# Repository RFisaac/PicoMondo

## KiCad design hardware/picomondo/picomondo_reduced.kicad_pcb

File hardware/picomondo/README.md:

# PicoMondo working project

Open `picomondo_reduced.kicad_pro` in KiCad 10.

This is the live design: v1 as ordered, plus changes made since. Anything here may be half-finished. To build or debug the boards that were actually made, use `../archive/v1-as-ordered/` instead.

## Changes since the v1 order

- **PSRAM (in progress, paused):** U16 APS6404L-3SQR (SOIC-8) and C71 100 nF added on the MCU sheet (2026-11-03) as an optional second QSPI memory. The schematic symbol is a W25Q128JVS borrowed for its pinout. It is placed on the board but not finished or checked.

## Sheets

| Sheet | Contents |
|---|---|
| `mcu_core` | RP2350B, VREG, crystal, flash, PSRAM, BOOTSEL/RESET, SWD |
| `barrel_input` | Barrel jack, PTC fuse, TVS, LM74502 reverse/overvoltage cut-off |
| `power_5v` | LMR33630B buck and the USB/barrel diode OR |
| `power_3v3` | AP2112K-3.3 LDO |
| `usb_c` | USB-C receptacle, CC resistors, ESD |
| `switched_output` | High-side P-FET output, INA226 monitor, fuse, flyback |
| `edgelock` | EdgeLock connectors, header holes, 100 Ω series resistors |
| `io_indicators` | Per-GPIO indicator LED ring |
| `neopixel` | NeoPixel buffer and connector, Qwiic |
| `board_support` | microSD, status/user/power LEDs, I2C pull-ups, test points |

## Libraries

- `lib/picomondo.pretty`: custom footprints (EdgeLock with 1.0 mm notches, header-hole and heavy-hole variants, RP2350 QFN-80 with thermal vias, polarity-marked VREG inductor, small-pad 0402).
- `lib/lcsc/`: parts converted from LCSC/EasyEDA with `easyeda2kicad`, with 3D models.
- `lib/MCU_RaspberryPi_RP2350.kicad_sym`: Raspberry Pi's RP2350 symbol.
- `JLCImport.*`: the JST-XH NeoPixel connector. One 3D model (`XY-SM04B-SRSS-TB.wrl`, the Qwiic connector) points at a global `${KICAD10_3RD_PARTY}` library and only shows if you have it installed.

## Fabrication

JLCPCB output is made with the Fabrication Toolkit plugin (settings in `fabrication-toolkit-options.json`). Generated `production/`, `jlcpcb/` and `bom/` folders are git-ignored here; the files that were actually ordered are in `../archive/v1-as-ordered/jlc_order_files/`.

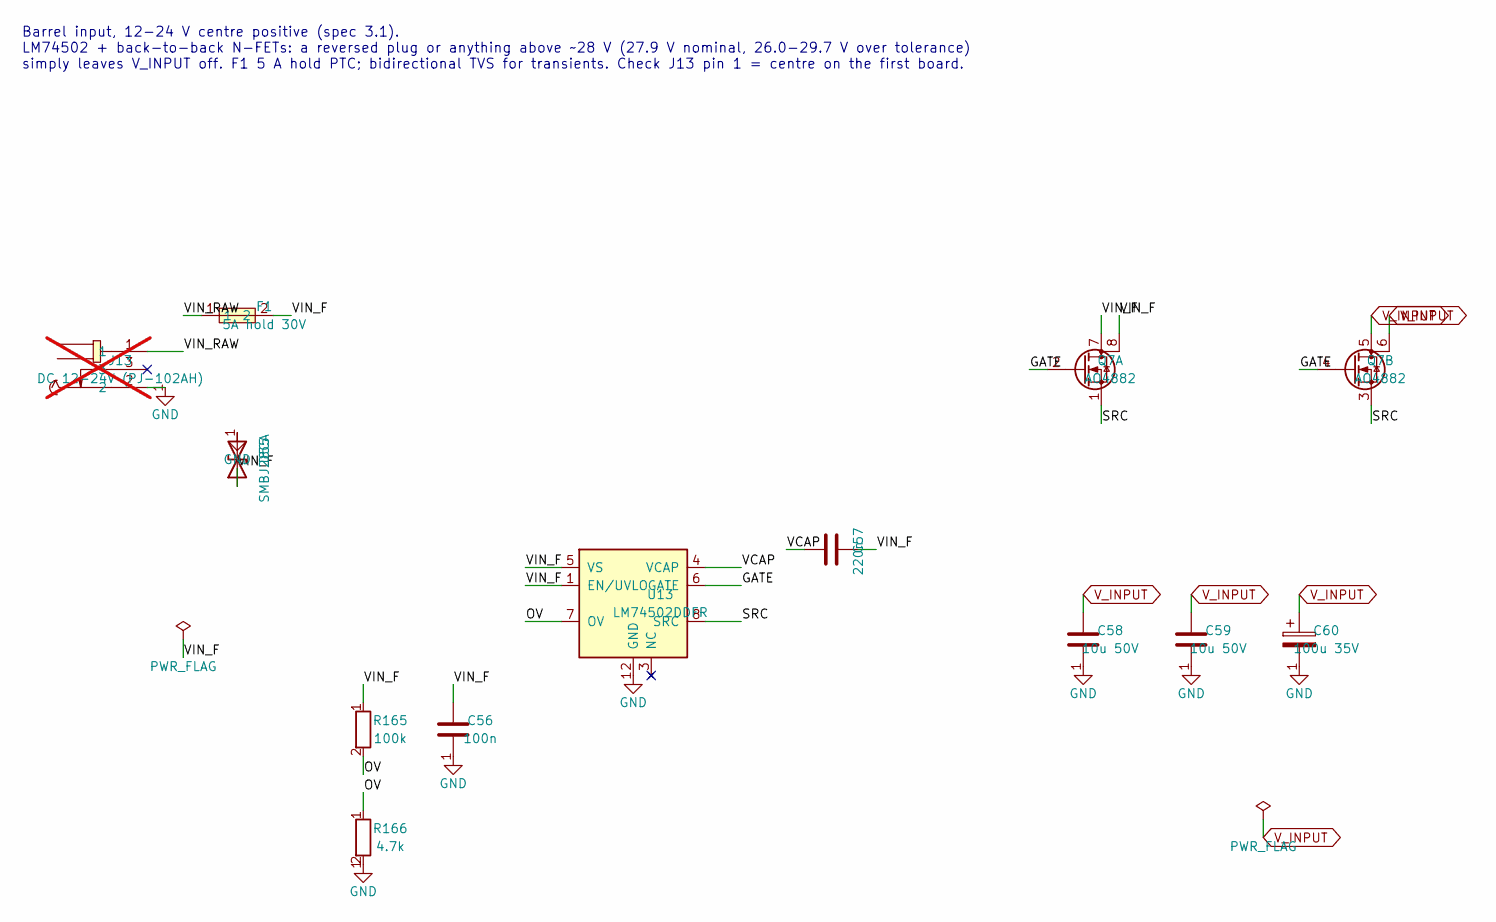
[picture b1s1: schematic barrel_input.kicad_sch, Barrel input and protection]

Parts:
C56: 100n; C_0402_1005Metric; MPN CL05B104KB54PNC; LCSC C307331
C57: 220n; C_0402_1005Metric; MPN C1005X7R1E224K050BB
C58, C59: 10u 50V; C_1206_3216Metric; MPN CL31A106KBHNNNE; LCSC C13585
C60: 100u 35V; CP_Elec_6.3x7.7; MPN VT1V101MCRE77; LCSC C294520
D55: SMBJ28CA; D_SMB; MPN SMBJ28CA; LCSC C8836
F1: 5A hold 30V; F2920; MPN 2920L500/30GR; LCSC C19078763
J13: DC 12-24V (PJ-102AH); DC-IN-TH_PJ-102AH; MPN PJ-102AH; LCSC C3096093; not fitted
Q7: AO4882; SOIC-8_3.9x4.9mm_P1.27mm; MPN AO4882; LCSC C477943
R165: 100k; R_0402_1005Metric; MPN 0402WGF1003TCE; LCSC C25741
R166: 4.7k; R_0402_1005Metric; MPN 0402WGF4701TCE; LCSC C25900
U13: LM74502DDFR; SOT-23-8; MPN LM74502DDFR; LCSC C3236215

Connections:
/Barrel input/GATE: Q7.2 (G), Q7.4 (G), U13.6 (GATE)
/Barrel input/OV: R165.2, R166.1, U13.7 (OV)
/Barrel input/SRC: Q7.1 (S), Q7.3 (S), U13.8 (SRC)
/Barrel input/VCAP: C57.1, U13.4 (VCAP)
/Barrel input/VIN_F: C56.1, C57.2, D55.1 (A1), F1.2, Q7.7 (D), Q7.8 (D), R165.1, U13.1 (EN/UVLO), U13.5 (VS)
/Barrel input/VIN_RAW: F1.1, J13.1
GND: C56.2, C58.2, C59.2, C60.2, D55.2 (A2), J13.2, R166.2, U13.2 (GND); also elsewhere on the board
V_INPUT: C58.1, C59.1, C60.1, Q7.5 (D), Q7.6 (D); also elsewhere on the board

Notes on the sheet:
Barrel input, 12-24 V centre positive (spec 3.1). LM74502 + back-to-back N-FETs: a reversed plug or anything above ~28 V (27.9 V nominal, 26.0-29.7 V over tolerance) simply leaves V_INPUT off. F1 5 A hold PTC; bidirectional TVS for transients. Check J13 pin 1 = centre on the first board.

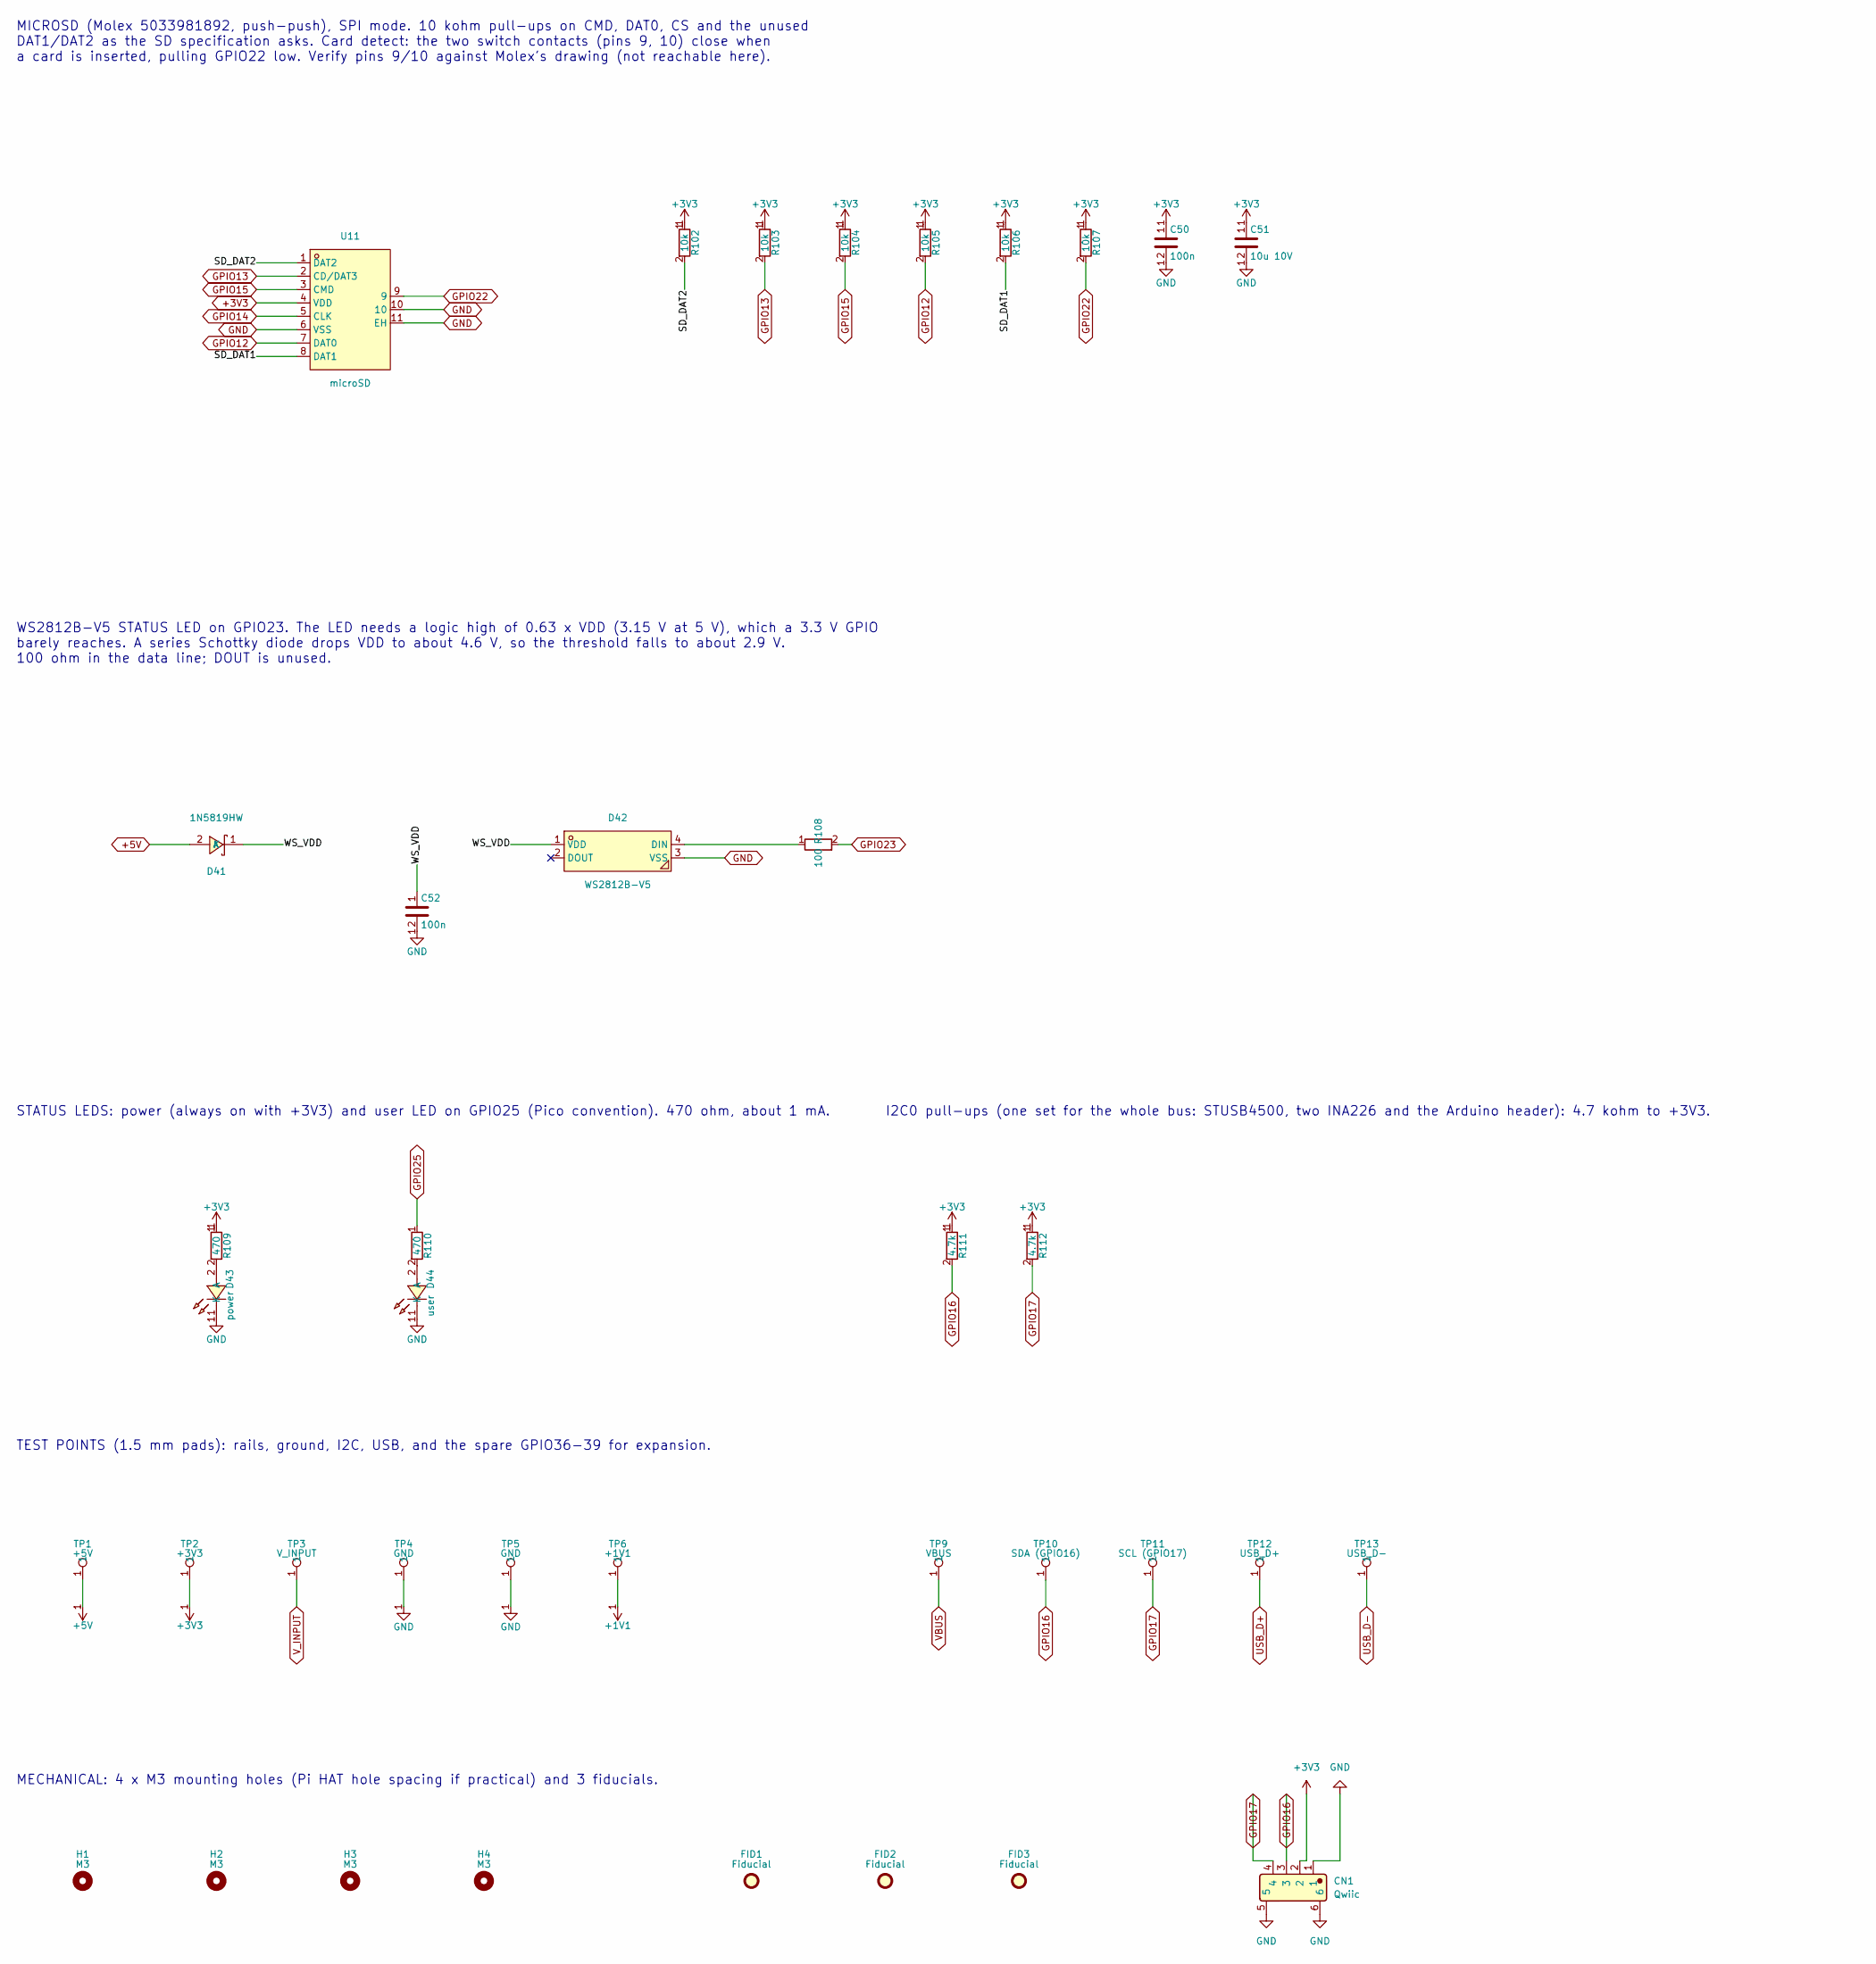
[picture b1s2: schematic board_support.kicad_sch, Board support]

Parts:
C50, C52: 100n; C_0402_1005Metric; MPN CL05B104KB54PNC; LCSC C307331
C51: 10u 10V; C_0805_2012Metric; MPN CL21A106KAYNNNE; LCSC C15850
CN1: Qwiic; XY-SM04B-SRSS-TB; MPN XY-SM04B-SRSS-TB; LCSC C51940130
D41: 1N5819HW; SOD-123_L2.7-W1.6-LS3.7-RD; MPN 1N5819HW-7-F; LCSC C82544
D42: WS2812B-V5; LED-SMD_4P-L5.0-W5.0-LS5.4-TL-1; MPN WS2812B-V5/W; LCSC C2874885
D43: power; LED-SMD_L1.0-W0.5-RD_WHITE; MPN LW QH8G-Q2OO-3K5L-1; LCSC C7220928
D44: user; LED-SMD_L1.0-W0.5-RD_WHITE; MPN LW QH8G-Q2OO-3K5L-1; LCSC C7220928
FID1, FID2, FID3: Fiducial; Fiducial_1mm_Mask2mm
H1, H2, H3, H4: M3; MountingHole_3.2mm_M3
R102, R103, R104, R105, R106, R107: 10k; R_0402_1005Metric; MPN 0402WGF1002TCE; LCSC C25744
R108: 100; R_0402_1005Metric; MPN 0402WGF1000TCE; LCSC C25076
R109, R110: 470; R_0402_1005Metric; MPN 0402WGF4700TCE; LCSC C25117
R111, R112: 4.7k; R_0402_1005Metric; MPN 0402WGF4701TCE; LCSC C25900
TP1: +5V; TestPoint_Pad_D1.5mm
TP2: +3V3; TestPoint_Pad_D1.5mm
TP3: V_INPUT; TestPoint_Pad_D1.5mm
TP4, TP5: GND; TestPoint_Pad_D1.5mm
TP6: +1V1; TestPoint_Pad_D1.5mm
TP9: VBUS; TestPoint_Pad_D1.5mm
TP10: SDA (GPIO16); TestPoint_Pad_D1.5mm
TP11: SCL (GPIO17); TestPoint_Pad_D1.5mm
TP12: USB_D+; TestPoint_Pad_D1.5mm
TP13: USB_D-; TestPoint_Pad_D1.5mm
U11: microSD; TF-SMD_503398-1892; MPN 5033981892; LCSC C428492

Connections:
+1V1: TP6.1 (1_1); also elsewhere on the board
+3V3: C50.1, C51.1, CN1.2, R102.1, R103.1, R104.1, R105.1, R106.1, R107.1, R109.1, R111.1, R112.1, TP2.1 (1_1), U11.4 (VDD); also elsewhere on the board
+5V: D41.2 (A), TP1.1 (1_1); also elsewhere on the board
/Board support/SD_DAT1: R106.2, U11.8 (DAT1)
/Board support/SD_DAT2: R102.2, U11.1 (DAT2)
/Board support/WS_VDD: C52.1, D41.1 (K), D42.1 (VDD)
GND: C50.2, C51.2, C52.2, CN1.1, CN1.5, CN1.6, D42.3 (VSS), D43.1 (K), D44.1 (K), TP4.1 (1_1), TP5.1 (1_1), U11.6 (VSS), U11.10, U11.11 (EH); also elsewhere on the board
GPIO12: R105.2, U11.7 (DAT0); also elsewhere on the board
GPIO13: R103.2, U11.2 (CD/DAT3); also elsewhere on the board
GPIO14: U11.5 (CLK); also elsewhere on the board
GPIO15: R104.2, U11.3 (CMD); also elsewhere on the board
GPIO16: CN1.3, R111.2, TP10.1 (1_1); also elsewhere on the board
GPIO17: CN1.4, R112.2, TP11.1 (1_1); also elsewhere on the board
GPIO22: R107.2, U11.9; also elsewhere on the board
GPIO23: R108.2; also elsewhere on the board
GPIO25: R110.1; also elsewhere on the board
unnamed: D42.4 (DIN), R108.1
unnamed: D43.2 (A), R109.2
unnamed: D44.2 (A), R110.2
USB_D+: TP12.1 (1_1); also elsewhere on the board
USB_D-: TP13.1 (1_1); also elsewhere on the board
VBUS: TP9.1 (1_1); also elsewhere on the board
V_INPUT: TP3.1 (1_1); also elsewhere on the board

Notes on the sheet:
MECHANICAL: 4 x M3 mounting holes (Pi HAT hole spacing if practical) and 3 fiducials.
I2C0 pull-ups (one set for the whole bus: STUSB4500, two INA226 and the Arduino header): 4.7 kohm to +3V3.
TEST POINTS (1.5 mm pads): rails, ground, I2C, USB, and the spare GPIO36-39 for expansion.
STATUS LEDS: power (always on with +3V3) and user LED on GPIO25 (Pico convention). 470 ohm, about 1 mA.
MICROSD (Molex 5033981892, push-push), SPI mode. 10 kohm pull-ups on CMD, DAT0, CS and the unused DAT1/DAT2 as the SD specification asks. Card detect: the two switch contacts (pins 9, 10) close when a card is inserted, pulling GPIO22 low. Verify pins 9/10 against Molex's drawing (not reachable here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
WS2812B-V5 STATUS LED on GPIO23. The LED needs a logic high of 0.63 x VDD (3.15 V at 5 V), which a 3.3 V GPIO barely reaches. A series Schottky diode drops VDD to about 4.6 V, so the threshold falls to about 2.9 V. 100 ohm in the data line; DOUT is unused.

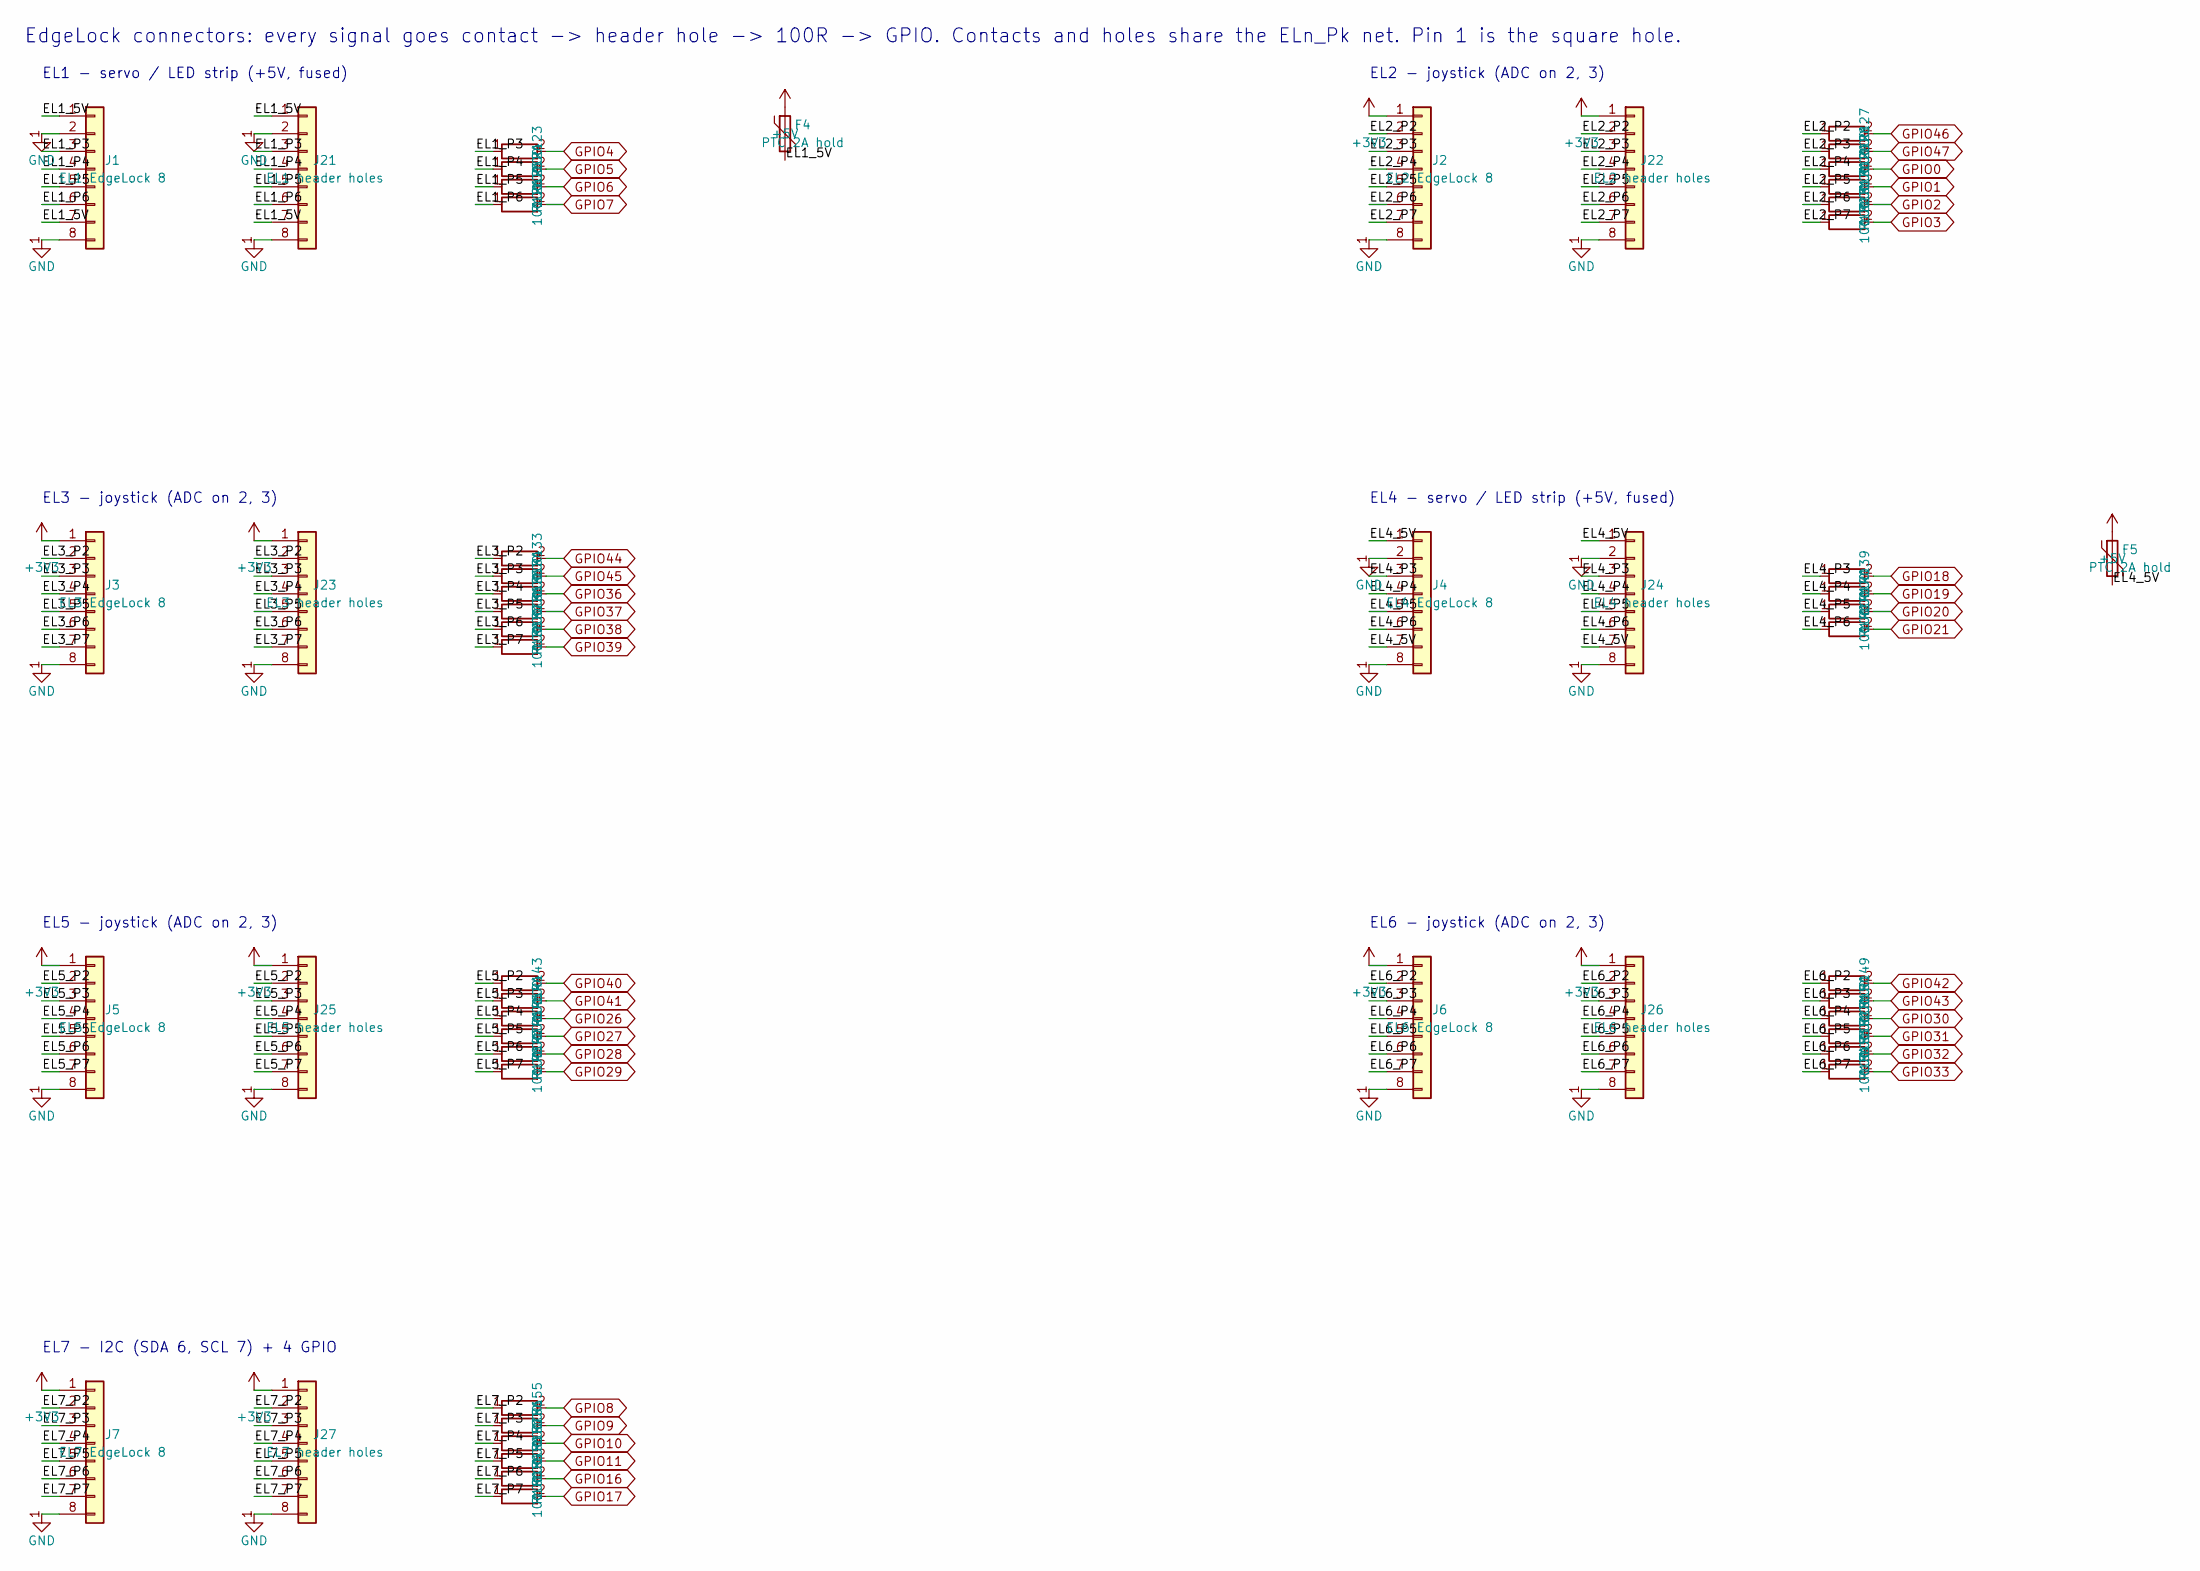
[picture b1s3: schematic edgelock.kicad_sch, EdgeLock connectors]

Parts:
F4, F5: PTC 2A hold; F1812; MPN SMD1812P200TF/16; LCSC C20812
J1: EL1 EdgeLock 8; EdgeLock_8ckt_Molex2008900108; MPN 2008900108
J2: EL2 EdgeLock 8; EdgeLock_8ckt_Molex2008900108; MPN 2008900108
J3: EL3 EdgeLock 8; EdgeLock_8ckt_Molex2008900108; MPN 2008900108
J4: EL4 EdgeLock 8; EdgeLock_8ckt_Molex2008900108; MPN 2008900108
J5: EL5 EdgeLock 8; EdgeLock_8ckt_Molex2008900108; MPN 2008900108
J6: EL6 EdgeLock 8; EdgeLock_8ckt_Molex2008900108; MPN 2008900108
J7: EL7 EdgeLock 8; EdgeLock_8ckt_Molex2008900108; MPN 2008900108
J21: EL1 header holes; EdgeLock_8ckt_HeaderHoles_Chevron
J22: EL2 header holes; EdgeLock_8ckt_HeaderHoles_Chevron
J23: EL3 header holes; EdgeLock_8ckt_HeaderHoles_Chevron
J24: EL4 header holes; EdgeLock_8ckt_HeaderHoles_Chevron
J25: EL5 header holes; EdgeLock_8ckt_HeaderHoles_Chevron
J26: EL6 header holes; EdgeLock_8ckt_HeaderHoles_Chevron
J27: EL7 header holes; EdgeLock_8ckt_HeaderHoles_Chevron
R123, R124, R125, R126, R127, R128, R129, R130, R131, R132, R133, R134, R135, R136, R137, R138, R139, R140, R141, R142, R143, R144, R145, R146, R147, R148, R149, R150, R151, R152, R153, R154, R155, R156, R157, R158, R159, R160: 100; R_0402_1005Metric; MPN 0402WGF1000TCE; LCSC C25076

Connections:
+3V3: J2.1, J3.1, J5.1, J6.1, J7.1, J22.1, J23.1, J25.1, J26.1, J27.1; also elsewhere on the board
+5V: F4.1, F5.1; also elsewhere on the board
/EdgeLock connectors/EL1_5V: F4.2, J1.1, J1.7, J21.1, J21.7
/EdgeLock connectors/EL1_P3: J1.3, J21.3, R123.1
/EdgeLock connectors/EL1_P4: J1.4, J21.4, R124.1
/EdgeLock connectors/EL1_P5: J1.5, J21.5, R125.1
/EdgeLock connectors/EL1_P6: J1.6, J21.6, R126.1
/EdgeLock connectors/EL2_P2: J2.2, J22.2, R127.1
/EdgeLock connectors/EL2_P3: J2.3, J22.3, R128.1
/EdgeLock connectors/EL2_P4: J2.4, J22.4, R129.1
/EdgeLock connectors/EL2_P5: J2.5, J22.5, R130.1
/EdgeLock connectors/EL2_P6: J2.6, J22.6, R131.1
/EdgeLock connectors/EL2_P7: J2.7, J22.7, R132.1
/EdgeLock connectors/EL3_P2: J3.2, J23.2, R133.1
/EdgeLock connectors/EL3_P3: J3.3, J23.3, R134.1
/EdgeLock connectors/EL3_P4: J3.4, J23.4, R135.1
/EdgeLock connectors/EL3_P5: J3.5, J23.5, R136.1
/EdgeLock connectors/EL3_P6: J3.6, J23.6, R137.1
/EdgeLock connectors/EL3_P7: J3.7, J23.7, R138.1
/EdgeLock connectors/EL4_5V: F5.2, J4.1, J4.7, J24.1, J24.7
/EdgeLock connectors/EL4_P3: J4.3, J24.3, R139.1
/EdgeLock connectors/EL4_P4: J4.4, J24.4, R140.1
/EdgeLock connectors/EL4_P5: J4.5, J24.5, R141.1
/EdgeLock connectors/EL4_P6: J4.6, J24.6, R142.1
/EdgeLock connectors/EL5_P2: J5.2, J25.2, R143.1
/EdgeLock connectors/EL5_P3: J5.3, J25.3, R144.1
/EdgeLock connectors/EL5_P4: J5.4, J25.4, R145.1
/EdgeLock connectors/EL5_P5: J5.5, J25.5, R146.1
/EdgeLock connectors/EL5_P6: J5.6, J25.6, R147.1
/EdgeLock connectors/EL5_P7: J5.7, J25.7, R148.1
/EdgeLock connectors/EL6_P2: J6.2, J26.2, R149.1
/EdgeLock connectors/EL6_P3: J6.3, J26.3, R150.1
/EdgeLock connectors/EL6_P4: J6.4, J26.4, R151.1
/EdgeLock connectors/EL6_P5: J6.5, J26.5, R152.1
/EdgeLock connectors/EL6_P6: J6.6, J26.6, R153.1
/EdgeLock connectors/EL6_P7: J6.7, J26.7, R154.1
/EdgeLock connectors/EL7_P2: J7.2, J27.2, R155.1
/EdgeLock connectors/EL7_P3: J7.3, J27.3, R156.1
/EdgeLock connectors/EL7_P4: J7.4, J27.4, R157.1
/EdgeLock connectors/EL7_P5: J7.5, J27.5, R158.1
/EdgeLock connectors/EL7_P6: J7.6, J27.6, R159.1
/EdgeLock connectors/EL7_P7: J7.7, J27.7, R160.1
GND: J1.2, J1.8, J2.8, J3.8, J4.2, J4.8, J5.8, J6.8, J7.8, J21.2, J21.8, J22.8, J23.8, J24.2, J24.8, J25.8, J26.8, J27.8; also elsewhere on the board
GPIO0: R129.2; also elsewhere on the board
GPIO1: R130.2; also elsewhere on the board
GPIO2: R131.2; also elsewhere on the board
GPIO3: R132.2; also elsewhere on the board
GPIO4: R123.2; also elsewhere on the board
GPIO5: R124.2; also elsewhere on the board
GPIO6: R125.2; also elsewhere on the board
GPIO7: R126.2; also elsewhere on the board
GPIO8: R155.2; also elsewhere on the board
GPIO9: R156.2; also elsewhere on the board
GPIO10: R157.2; also elsewhere on the board
GPIO11: R158.2; also elsewhere on the board
GPIO16: R159.2; also elsewhere on the board
GPIO17: R160.2; also elsewhere on the board
GPIO18: R139.2; also elsewhere on the board
GPIO19: R140.2; also elsewhere on the board
GPIO20: R141.2; also elsewhere on the board
GPIO21: R142.2; also elsewhere on the board
GPIO26: R145.2; also elsewhere on the board
GPIO27: R146.2; also elsewhere on the board
GPIO28: R147.2; also elsewhere on the board
GPIO29: R148.2; also elsewhere on the board
GPIO30: R151.2; also elsewhere on the board
GPIO31: R152.2; also elsewhere on the board
GPIO32: R153.2; also elsewhere on the board
GPIO33: R154.2; also elsewhere on the board
GPIO36: R135.2; also elsewhere on the board
GPIO37: R136.2; also elsewhere on the board
GPIO38: R137.2; also elsewhere on the board
GPIO39: R138.2; also elsewhere on the board
GPIO40: R143.2; also elsewhere on the board
GPIO41: R144.2; also elsewhere on the board
GPIO42: R149.2; also elsewhere on the board
GPIO43: R150.2; also elsewhere on the board
GPIO44: R133.2; also elsewhere on the board
GPIO45: R134.2; also elsewhere on the board
GPIO46: R127.2; also elsewhere on the board
GPIO47: R128.2; also elsewhere on the board

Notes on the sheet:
EL6 - joystick (ADC on 2, 3)
EL5 - joystick (ADC on 2, 3)
EL2 - joystick (ADC on 2, 3)
EL4 - servo / LED strip (+5V, fused)
EdgeLock connectors: every signal goes contact -> header hole -> 100R -> GPIO. Contacts and holes share the ELn_Pk net. Pin 1 is the square hole.
EL1 - servo / LED strip (+5V, fused)
EL7 - I2C (SDA 6, SCL 7) + 4 GPIO
EL3 - joystick (ADC on 2, 3)

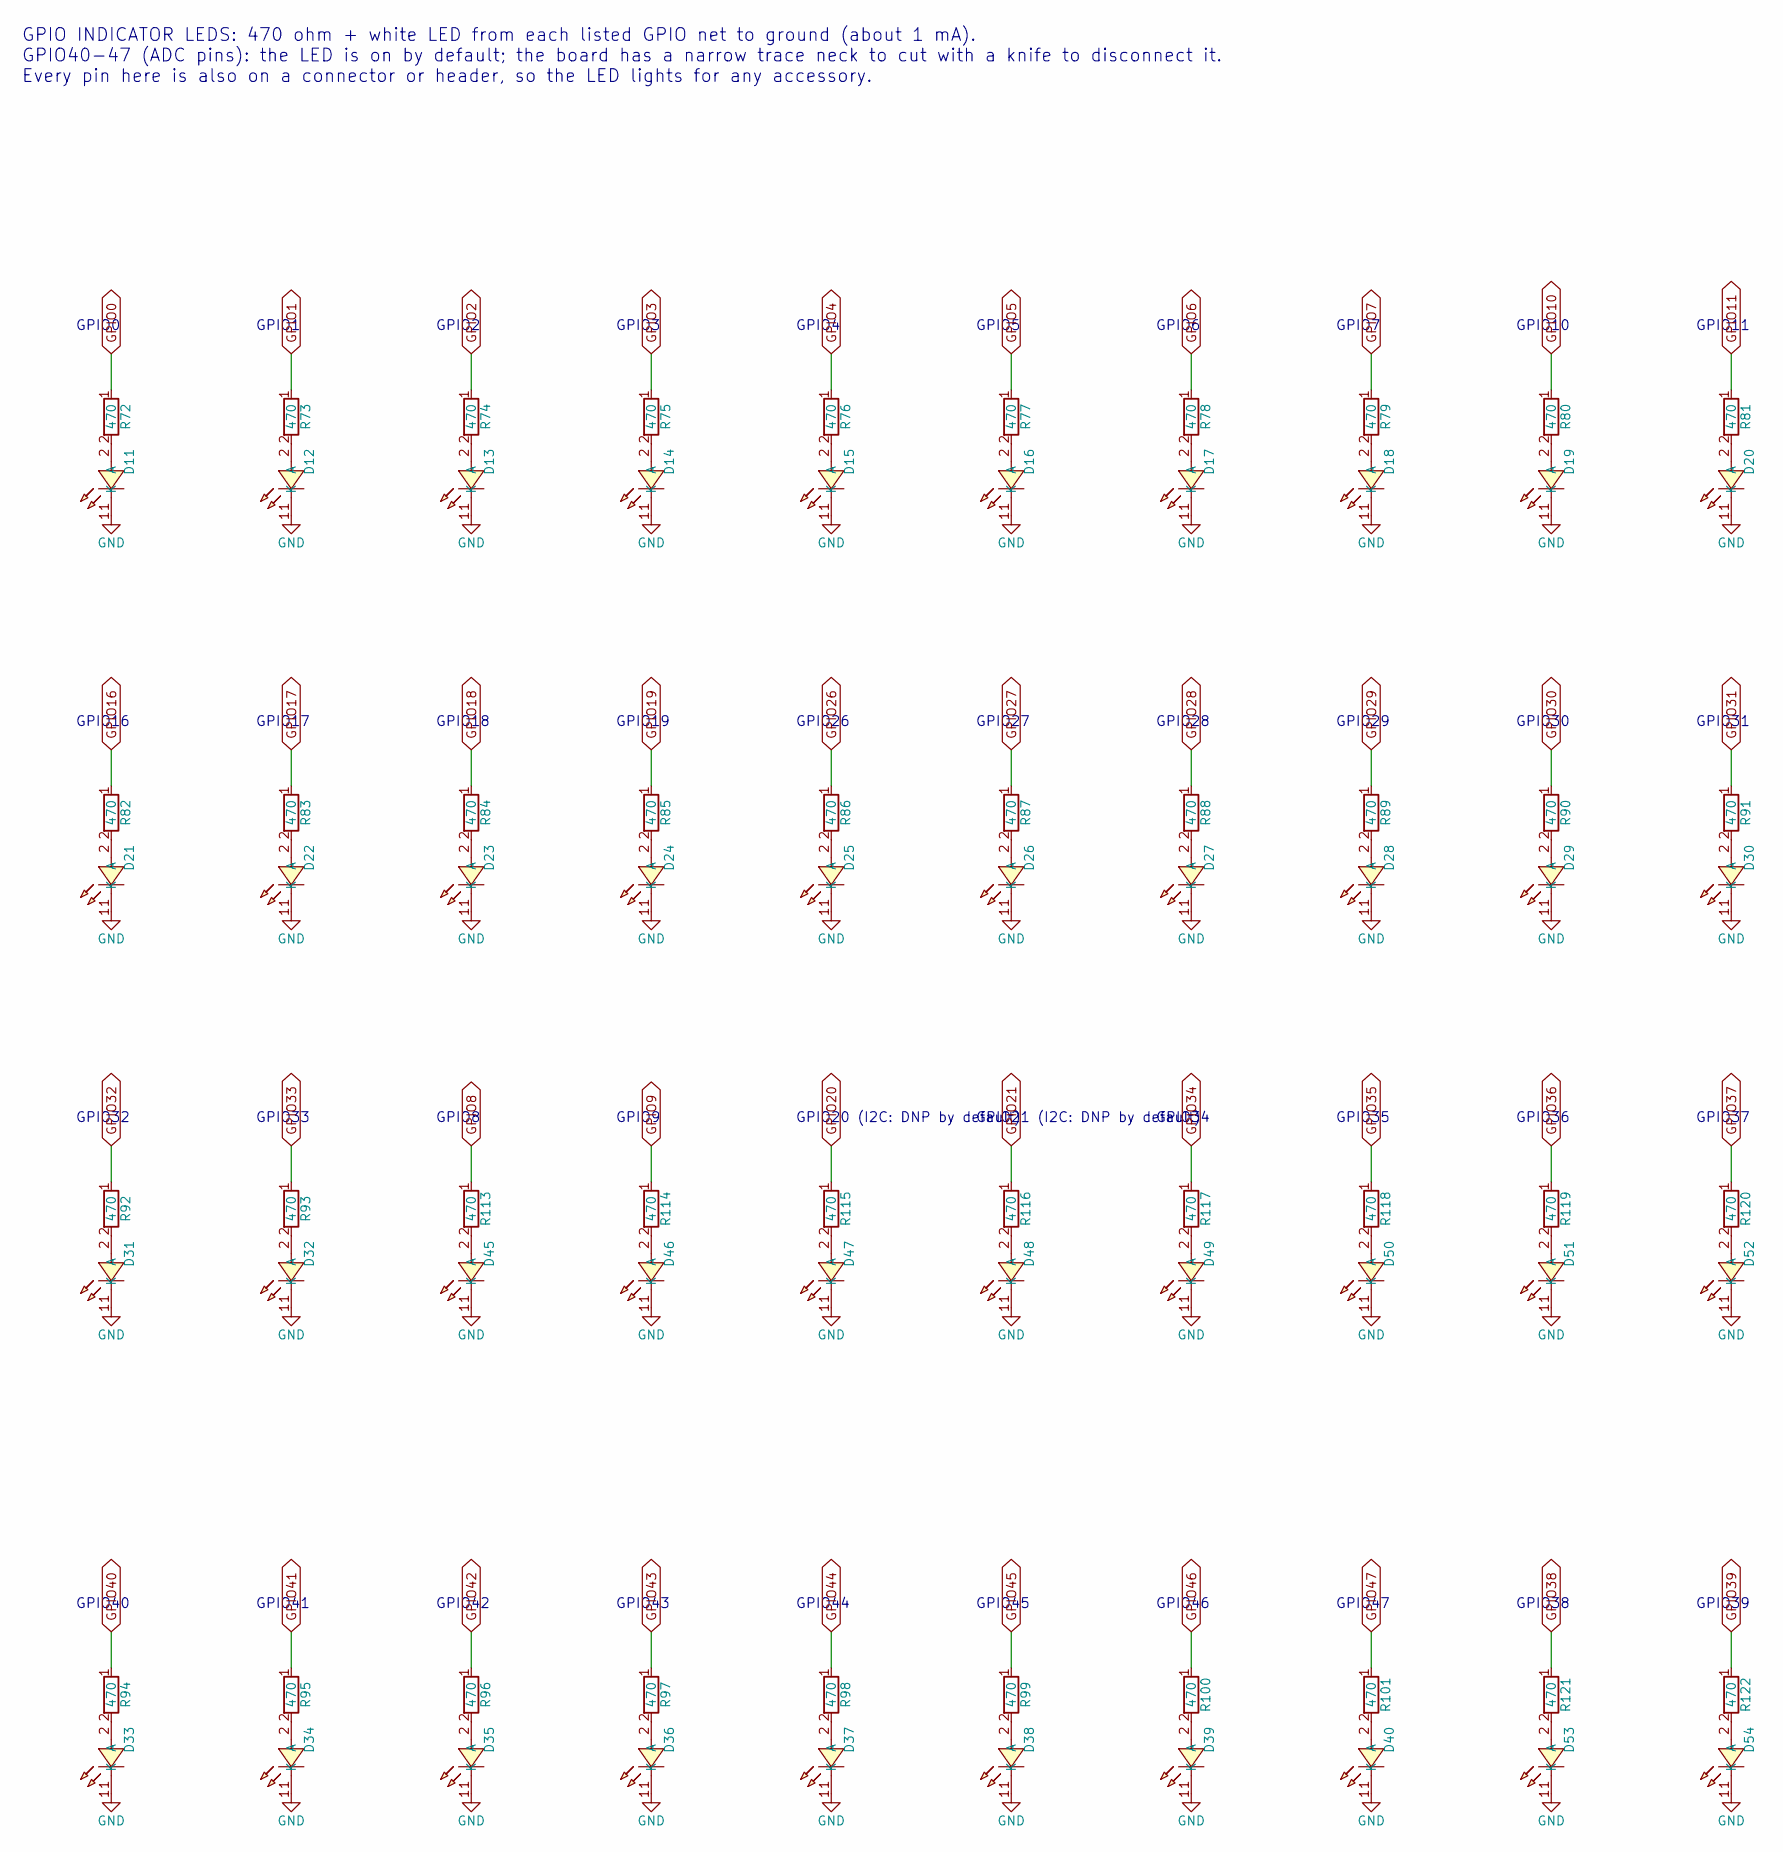
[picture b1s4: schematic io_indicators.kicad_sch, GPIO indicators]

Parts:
D11, D12, D13, D14, D15, D16, D17, D18, D19, D20, D21, D22, D23, D24, D25, D26, D27, D28, D29, D30, D31, D32, D33, D34, D35, D36, D37, D38, D39, D40, D45, D46, D47, D48, D49, D50, D51, D52, D53, D54: white; LED-SMD_L1.0-W0.5-RD_WHITE; MPN LW QH8G-Q2OO-3K5L-1; LCSC C7220928
R72, R73, R74, R75, R76, R77, R78, R79, R80, R81, R82, R83, R84, R85, R86, R87, R88, R89, R90, R91, R92, R93, R94, R95, R96, R97, R98, R99, R100, R101, R113, R114, R115, R116, R117, R118, R119, R120, R121, R122: 470; R_0402_1005Metric; MPN 0402WGF4700TCE; LCSC C25117

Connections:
GND: D11.1 (K), D12.1 (K), D13.1 (K), D14.1 (K), D15.1 (K), D16.1 (K), D17.1 (K), D18.1 (K), D19.1 (K), D20.1 (K), D21.1 (K), D22.1 (K), D23.1 (K), D24.1 (K), D25.1 (K), D26.1 (K), D27.1 (K), D28.1 (K), D29.1 (K), D30.1 (K), D31.1 (K), D32.1 (K), D33.1 (K), D34.1 (K), D35.1 (K), D36.1 (K), D37.1 (K), D38.1 (K), D39.1 (K), D40.1 (K), D45.1 (K), D46.1 (K), D47.1 (K), D48.1 (K), D49.1 (K), D50.1 (K), D51.1 (K), D52.1 (K), D53.1 (K), D54.1 (K); also elsewhere on the board
GPIO0: R72.1; also elsewhere on the board
GPIO1: R73.1; also elsewhere on the board
GPIO2: R74.1; also elsewhere on the board
GPIO3: R75.1; also elsewhere on the board
GPIO4: R76.1; also elsewhere on the board
GPIO5: R77.1; also elsewhere on the board
GPIO6: R78.1; also elsewhere on the board
GPIO7: R79.1; also elsewhere on the board
GPIO8: R113.1; also elsewhere on the board
GPIO9: R114.1; also elsewhere on the board
GPIO10: R80.1; also elsewhere on the board
GPIO11: R81.1; also elsewhere on the board
GPIO16: R82.1; also elsewhere on the board
GPIO17: R83.1; also elsewhere on the board
GPIO18: R84.1; also elsewhere on the board
GPIO19: R85.1; also elsewhere on the board
GPIO20: R115.1; also elsewhere on the board
GPIO21: R116.1; also elsewhere on the board
GPIO26: R86.1; also elsewhere on the board
GPIO27: R87.1; also elsewhere on the board
GPIO28: R88.1; also elsewhere on the board
GPIO29: R89.1; also elsewhere on the board
GPIO30: R90.1; also elsewhere on the board
GPIO31: R91.1; also elsewhere on the board
GPIO32: R92.1; also elsewhere on the board
GPIO33: R93.1; also elsewhere on the board
GPIO34: R117.1; also elsewhere on the board
GPIO35: R118.1; also elsewhere on the board
GPIO36: R119.1; also elsewhere on the board
GPIO37: R120.1; also elsewhere on the board
GPIO38: R121.1; also elsewhere on the board
GPIO39: R122.1; also elsewhere on the board
GPIO40: R94.1; also elsewhere on the board
GPIO41: R95.1; also elsewhere on the board
GPIO42: R96.1; also elsewhere on the board
GPIO43: R97.1; also elsewhere on the board
GPIO44: R98.1; also elsewhere on the board
GPIO45: R99.1; also elsewhere on the board
GPIO46: R100.1; also elsewhere on the board
GPIO47: R101.1; also elsewhere on the board
unnamed: D11.2 (A), R72.2
unnamed: D12.2 (A), R73.2
unnamed: D13.2 (A), R74.2
unnamed: D14.2 (A), R75.2
unnamed: D15.2 (A), R76.2
unnamed: D16.2 (A), R77.2
unnamed: D17.2 (A), R78.2
unnamed: D18.2 (A), R79.2
unnamed: D19.2 (A), R80.2
unnamed: D20.2 (A), R81.2
unnamed: D21.2 (A), R82.2
unnamed: D22.2 (A), R83.2
unnamed: D23.2 (A), R84.2
unnamed: D24.2 (A), R85.2
unnamed: D25.2 (A), R86.2
unnamed: D26.2 (A), R87.2
unnamed: D27.2 (A), R88.2
unnamed: D28.2 (A), R89.2
unnamed: D29.2 (A), R90.2
unnamed: D30.2 (A), R91.2
unnamed: D31.2 (A), R92.2
unnamed: D32.2 (A), R93.2
unnamed: D33.2 (A), R94.2
unnamed: D34.2 (A), R95.2
unnamed: D35.2 (A), R96.2
unnamed: D36.2 (A), R97.2
unnamed: D37.2 (A), R98.2
unnamed: D38.2 (A), R99.2
unnamed: D39.2 (A), R100.2
unnamed: D40.2 (A), R101.2
unnamed: D45.2 (A), R113.2
unnamed: D46.2 (A), R114.2
unnamed: D47.2 (A), R115.2
unnamed: D48.2 (A), R116.2
unnamed: D49.2 (A), R117.2
unnamed: D50.2 (A), R118.2
unnamed: D51.2 (A), R119.2
unnamed: D52.2 (A), R120.2
unnamed: D53.2 (A), R121.2
unnamed: D54.2 (A), R122.2

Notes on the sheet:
GPIO37
GPIO41
GPIO33
GPIO18
GPIO21 (I2C: DNP by default)
GPIO11
GPIO16
GPIO34
GPIO38
GPIO7
GPIO9
GPIO19
GPIO44
GPIO3
GPIO36
GPIO5
GPIO43
GPIO2
GPIO10
GPIO29
GPIO47
GPIO1
GPIO46
GPIO40
GPIO32
GPIO20 (I2C: DNP by default)
GPIO0
GPIO39
GPIO45
GPIO8
GPIO INDICATOR LEDS: 470 ohm + white LED from each listed GPIO net to ground (about 1 mA). GPIO40-47 (ADC pins): the LED is on by default; the board has a narrow trace neck to cut with a knife to disconnect it. Every pin here is also on a connector or header, so the LED lights for any accessory.
GPIO28
GPIO4
GPIO42
GPIO35
GPIO26
GPIO17
GPIO30
GPIO31
GPIO27
